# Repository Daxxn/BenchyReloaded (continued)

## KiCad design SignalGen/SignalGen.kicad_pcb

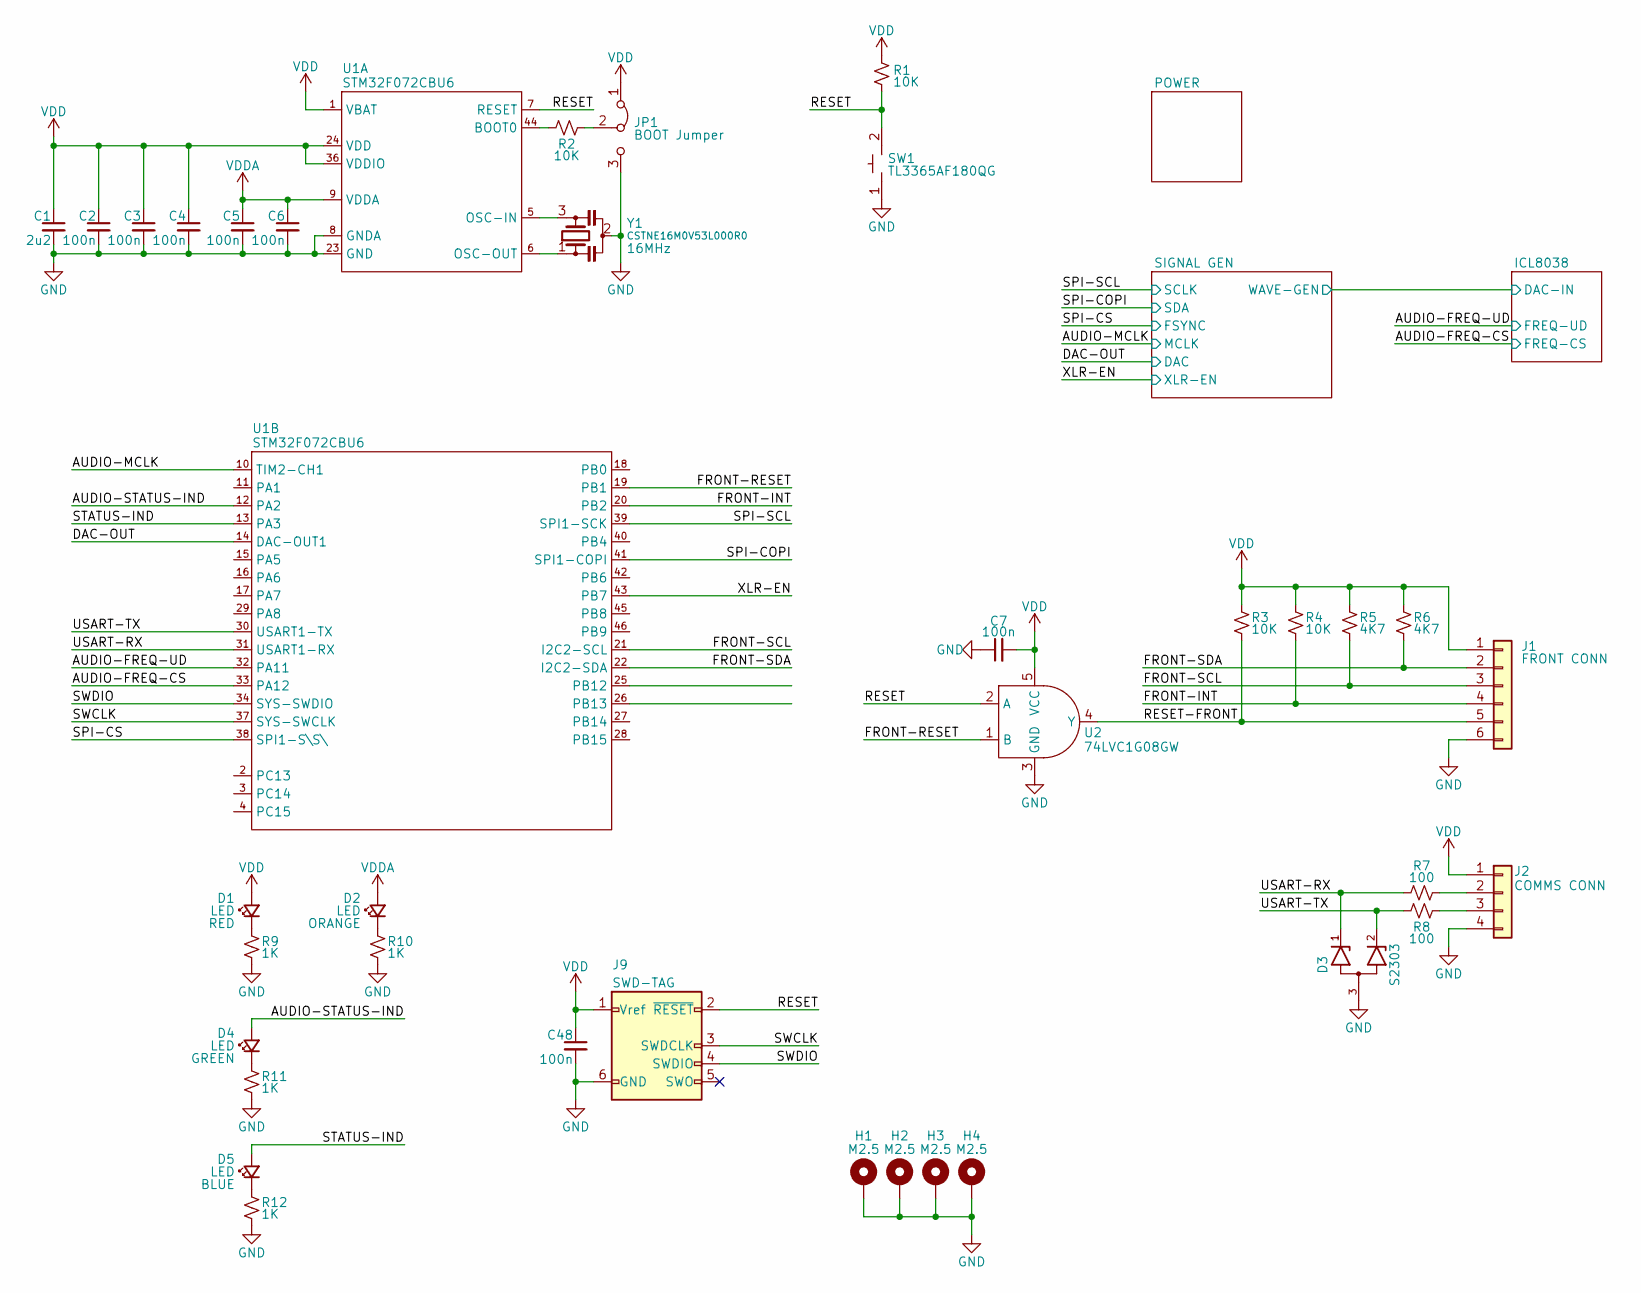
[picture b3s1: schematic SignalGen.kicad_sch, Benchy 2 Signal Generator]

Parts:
C1: 2u2; CAP_0402
C2, C3, C4, C5, C6, C7, C48: 100n; CAP_0402
D1, D2, D4, D5: LED; LED_0603_1608Metric
D3: S2303; SOT-23-3
H1, H2, H3, H4: M2.5; MountingHole_2.7mm_M2.5_DIN965_Pad
J1: FRONT CONN; JST_XH_B6B-XH-A_1x06_P2.50mm_Vertical
J2: COMMS CONN; JST_XH_B4B-XH-A_1x04_P2.50mm_Vertical
J9: SWD-TAG; Tag-Connect_TC2030-IDC-FP_2x03_P1.27mm_Vertical
JP1: BOOT Jumper; PinHeader_1x03_P2.54mm_Vertical
R1, R2, R3, R4: 10K; RES_0402
R5, R6: 4K7; RES_0402
R7, R8: 100; RES_0402
R9, R10, R11, R12: 1K; RES_0402
SW1: TL3365AF180QG
U1: STM32F072CBU6; QFN-48-1EP_7x7mm_P0.5mm_EP5.6x5.6mm
U2: 74LVC1G08GW; SOT-353_SC-70-5
Y1: CSTNE16M0V53L000R0; Resonator_SMD_3Pin_3.0x1.1mm

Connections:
/AUDIO-FREQ-CS: U1.33 (PA12); also elsewhere on the board
/AUDIO-FREQ-UD: U1.32 (PA11); also elsewhere on the board
/AUDIO-MCLK: U1.10 (TIM2-CH1); also elsewhere on the board
/AUDIO-STATUS-IND: D4.2 (A), U1.12 (PA2)
/DAC-OUT: U1.14 (DAC-OUT1); also elsewhere on the board
/FRONT-INT: J1.4, R4.2, U1.20 (PB2)
/FRONT-RESET: U1.19 (PB1), U2.1 (B)
/FRONT-SCL: J1.3, R5.2, U1.21 (I2C2-SCL)
/FRONT-SDA: J1.2, R6.2, U1.22 (I2C2-SDA)
/RESET: J9.2 (~RESET), R1.2, SW1.2, U1.7 (RESET), U2.2 (A)
/RESET-FRONT: J1.5, R3.2, U2.4 (Y)
/SPI-COPI: U1.41 (SPI1-COPI); also elsewhere on the board
/SPI-CS: U1.38 (SPI1-S\S\); also elsewhere on the board
/SPI-SCL: U1.39 (SPI1-SCK); also elsewhere on the board
/STATUS-IND: D5.2 (A), U1.13 (PA3)
/SWCLK: J9.3 (SWDCLK), U1.37 (SYS-SWCLK)
/SWDIO: J9.4 (SWDIO), U1.34 (SYS-SWDIO)
/USART-RX: D3.1 (A), R7.1, U1.31 (USART1-RX)
/USART-TX: D3.2 (B), R8.2, U1.30 (USART1-TX)
/XLR-EN: U1.43 (PB7)
GND: C1.2, C2.2, C3.2, C4.2, C5.2, C6.2, C7.1, C48.2, D3.3 (COM), H1.1, H2.1, H3.1, H4.1, J1.6, J2.4, J9.6 (GND), JP1.3 (B), R9.2, R10.2, R11.2, R12.2, SW1.1, U1.8 (GNDA), U1.23 (GND), U1.35 (GND), U1.47 (GND), U1.49 (GND), U2.3 (GND), Y1.2; also elsewhere on the board
unnamed: D1.1 (K), R9.1
unnamed: D2.1 (K), R10.1
unnamed: D4.1 (K), R11.1
unnamed: D5.1 (K), R12.1
unnamed: J2.2, R7.2
unnamed: J2.3, R8.1
unnamed: JP1.2 (C), R2.1
unnamed: R2.2, U1.44 (BOOT0)
unnamed: U1.5 (OSC-IN), Y1.3
unnamed: U1.6 (OSC-OUT), Y1.1
VDD: C1.1, C2.1, C3.1, C4.1, C7.2, C48.1, D1.2 (A), J1.1, J2.1, J9.1 (Vref), JP1.1 (A), R1.1, R3.1, R4.1, R5.1, R6.1, U1.1 (VBAT), U1.24 (VDD), U1.36 (VDDIO), U1.48 (VDD), U2.5 (VCC); also elsewhere on the board
VDDA: C5.1, C6.1, D2.2 (A), U1.9 (VDDA); also elsewhere on the board

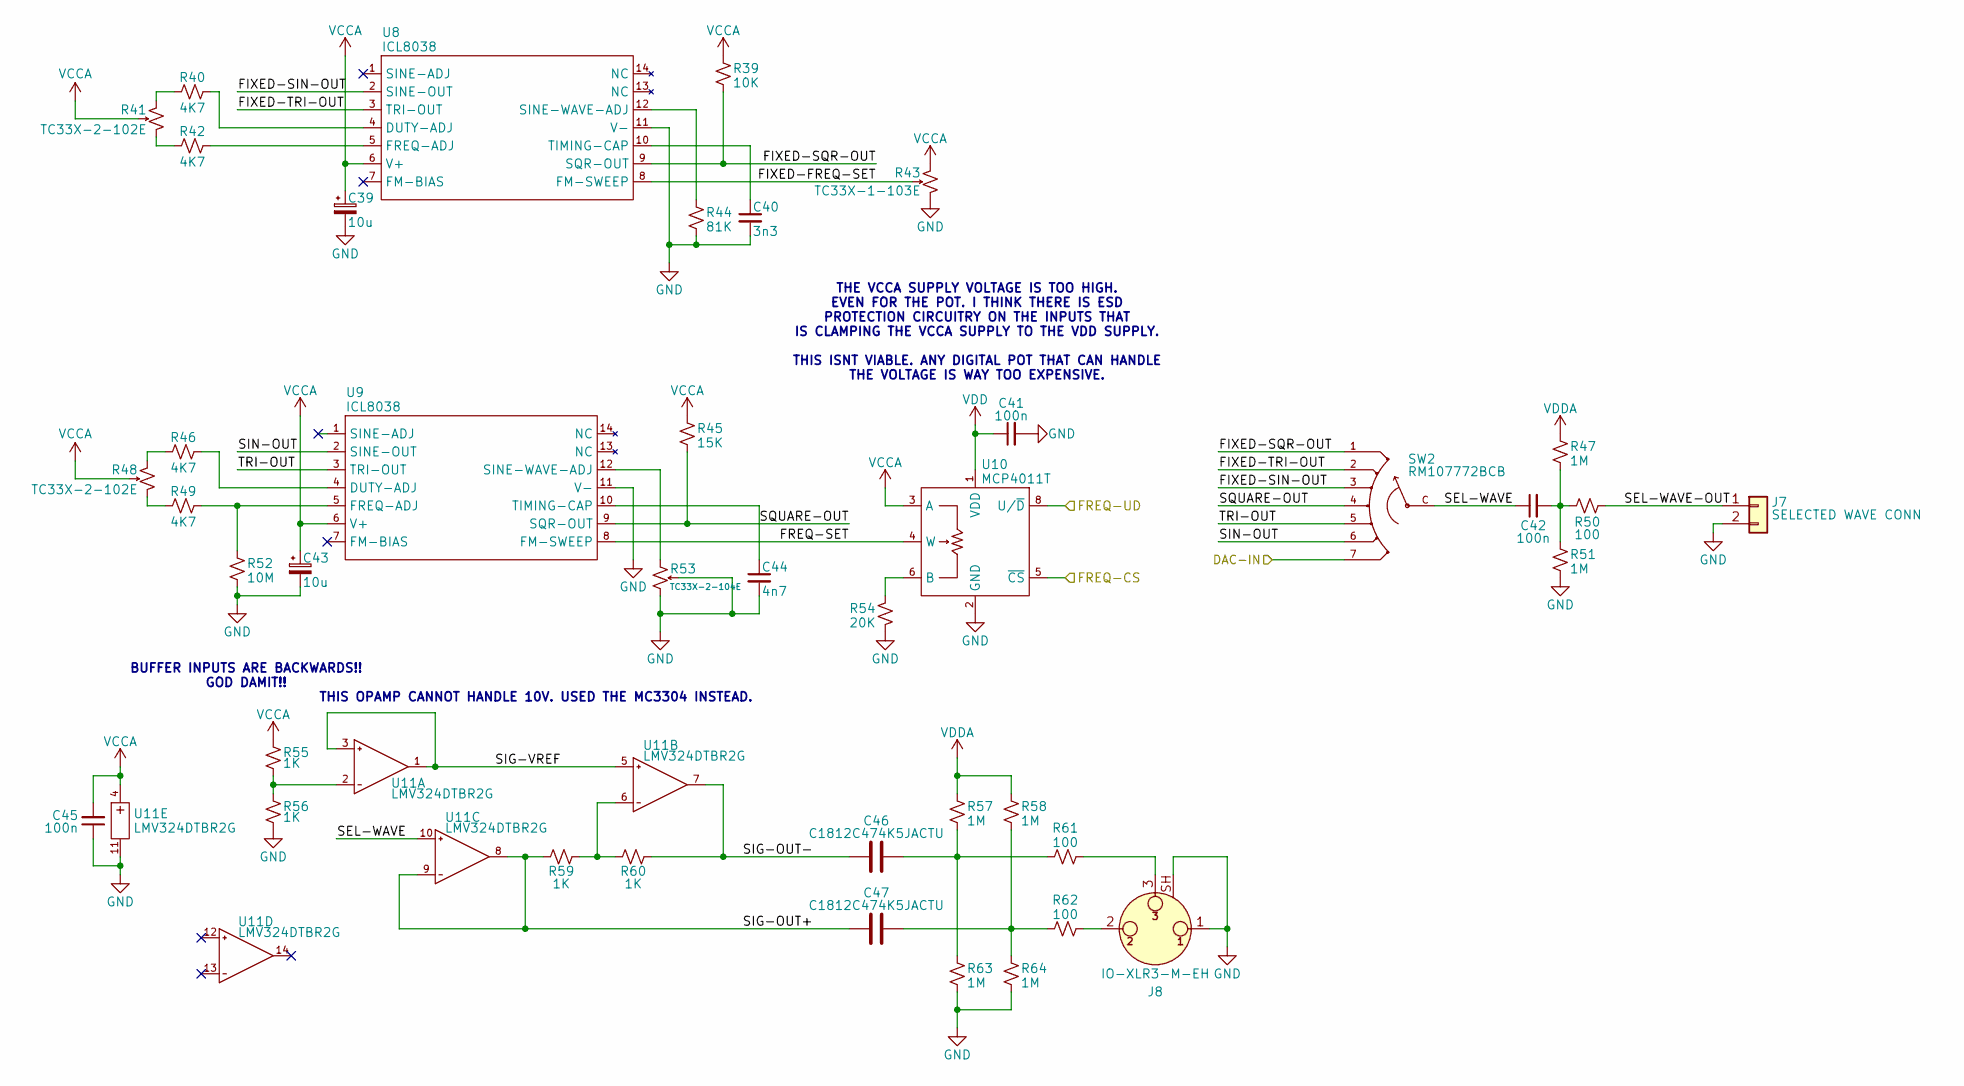
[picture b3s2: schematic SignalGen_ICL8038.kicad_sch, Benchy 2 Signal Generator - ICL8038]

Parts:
C39, C43: 10u; CAP_TAN_1206
C40: 3n3; CAP_0402
C41, C42, C45: 100n; CAP_0402
C44: 4n7; CAP_0402
C46, C47: C1812C474K5JACTU; CAP_1812
J7: SELECTED WAVE CONN; S2B-XH-A; Part Number 0311-0000-00001
J8: IO-XLR3-M-EH
R39: 10K; RES_0402
R40, R42, R46, R49: 4K7; RES_0402
R41, R48: TC33X-2-102E; Bourns_TC33X
R43: TC33X-1-103E; Bourns_TC33X
R44: 81K; RES_0402
R45: 15K; RES_0402
R47, R51, R57, R58, R63, R64: 1M; RES_0402
R50, R61, R62: 100; RES_0402
R52: 10M; RES_0402
R53: TC33X-2-104E; Bourns_TC33X
R54: 20K; RES_0402
R55, R56, R59, R60: 1K; RES_0402
SW2: RM107772BCB; RM104772BCB
U8, U9: ICL8038; DIP-14_W7.62mm
U10: MCP4011T; SOIC-8_3.9x4.9mm_P1.27mm
U11: LMV324DTBR2G; TSSOP-14_4.4x5mm_P0.65mm

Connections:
/AUDIO-FREQ-CS: U10.5 (~CS); also elsewhere on the board
/AUDIO-FREQ-UD: U10.8 (U/~D); also elsewhere on the board
/ICL8038/FIXED-FREQ-SET: R43.2, U8.8 (FM-SWEEP)
/ICL8038/FIXED-SIN-OUT: SW2.3, U8.2 (SINE-OUT)
/ICL8038/FIXED-SQR-OUT: R39.1, SW2.1, U8.9 (SQR-OUT)
/ICL8038/FIXED-TRI-OUT: SW2.2, U8.3 (TRI-OUT)
/ICL8038/FREQ-SET: U9.8 (FM-SWEEP), U10.4 (W)
/ICL8038/SEL-WAVE: C42.1, SW2.C, U11.10 (IN3+)
/ICL8038/SEL-WAVE-OUT: J7.1, R50.1
/ICL8038/SIG-OUT+: C47.1, R59.2, U11.8 (OUT3), U11.9 (IN3-)
/ICL8038/SIG-OUT-: C46.1, R60.1, U11.7 (OUT2)
/ICL8038/SIG-VREF: U11.1 (OUT1), U11.3 (IN1+), U11.5 (IN2+)
/ICL8038/SIN-OUT: SW2.6, U9.2 (SINE-OUT)
/ICL8038/SQUARE-OUT: R45.1, SW2.4, U9.9 (SQR-OUT)
/ICL8038/TRI-OUT: SW2.5, U9.3 (TRI-OUT)
/SIGNAL GEN/WAVE-GEN: SW2.7; also elsewhere on the board
GND: C39.2, C40.2, C41.2, C43.2, C44.2, C45.1, J7.2, J8.1, J8.SH, R43.3, R44.1, R51.1, R52.1, R53.2, R53.3, R54.1, R56.1, R63.1, R64.1, U8.11 (V-), U9.11 (V-), U10.2 (GND), U11.11 (V-); also elsewhere on the board
unnamed: C42.2, R47.1, R50.2, R51.2
unnamed: C46.2, R57.1, R61.1, R63.2
unnamed: C47.2, R58.1, R62.1, R64.2
unnamed: J8.2, R62.2
unnamed: J8.3, R61.2
unnamed: R40.1, R41.1
unnamed: R41.3, R42.1
unnamed: R46.1, R48.1
unnamed: R48.3, R49.1
unnamed: R40.2, U8.4 (DUTY-ADJ)
unnamed: R42.2, U8.5 (FREQ-ADJ)
unnamed: R44.2, U8.12 (SINE-WAVE-ADJ)
unnamed: C40.1, U8.10 (TIMING-CAP)
unnamed: R46.2, U9.4 (DUTY-ADJ)
unnamed: R49.2, R52.2, U9.5 (FREQ-ADJ)
unnamed: R53.1, U9.12 (SINE-WAVE-ADJ)
unnamed: C44.1, U9.10 (TIMING-CAP)
unnamed: R54.2, U10.6 (B)
unnamed: R55.1, R56.2, U11.2 (IN1-)
unnamed: R59.1, R60.2, U11.6 (IN2-)
VCCA: C39.1, C43.1, C45.2, R39.2, R41.2, R43.1, R45.2, R48.2, R55.2, U8.6 (V+), U9.6 (V+), U10.3 (A), U11.4 (V+); also elsewhere on the board
VDD: C41.1, U10.1 (VDD); also elsewhere on the board
VDDA: R47.2, R57.2, R58.2; also elsewhere on the board

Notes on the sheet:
BUFFER INPUTS ARE BACKWARDS!! GOD DAMIT!!
THIS OPAMP CANNOT HANDLE 10V. USED THE MC3304 INSTEAD.
THE VCCA SUPPLY VOLTAGE IS TOO HIGH. EVEN FOR THE POT. I THINK THERE IS ESD PROTECTION CIRCUITRY ON THE INPUTS THAT IS CLAMPING THE VCCA SUPPLY TO THE VDD SUPPLY. THIS ISNT VIABLE. ANY DIGITAL POT THAT CAN HANDLE THE VOLTAGE IS WAY TOO EXPENSIVE.

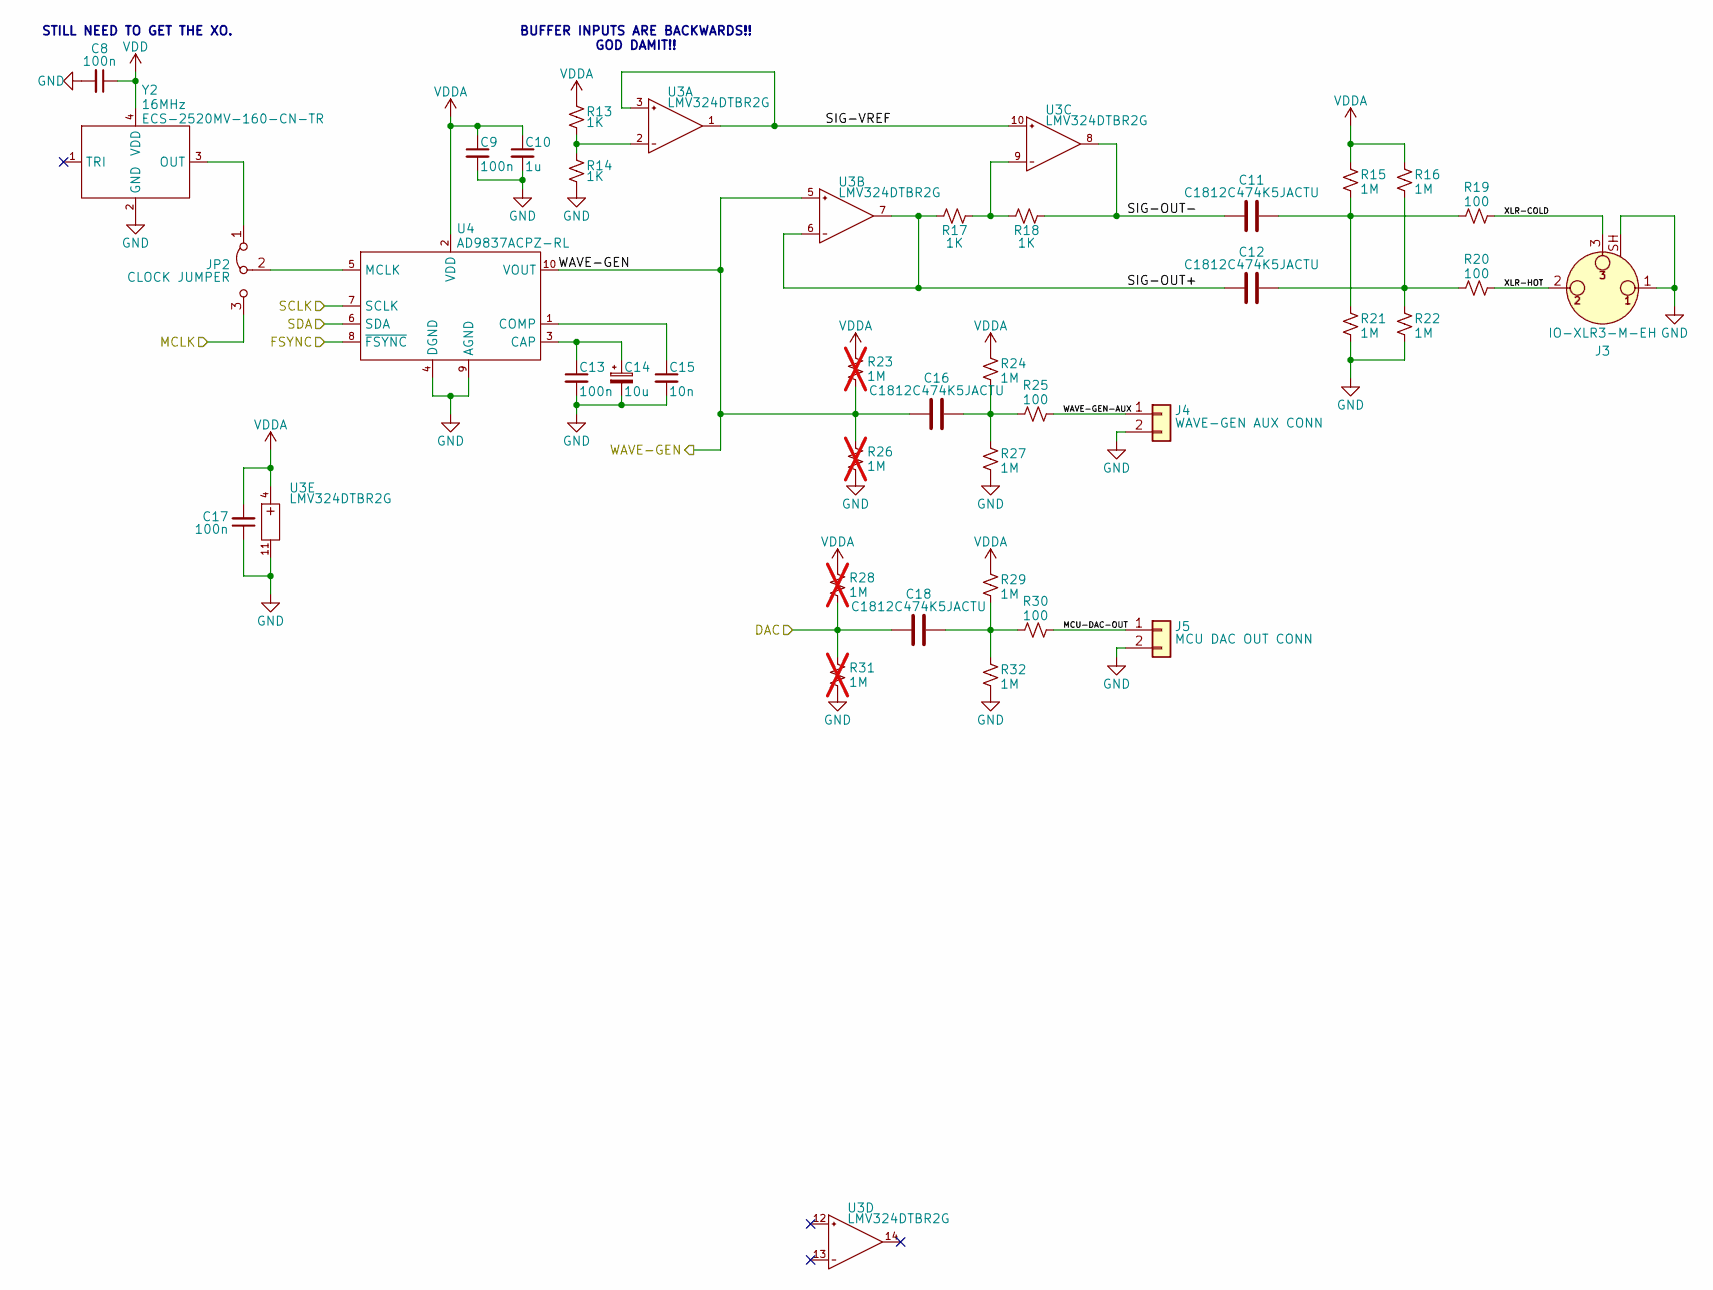
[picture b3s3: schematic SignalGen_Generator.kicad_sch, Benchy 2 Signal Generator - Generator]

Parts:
C8, C9, C13, C17: 100n; CAP_0402
C10: 1u; CAP_0402
C11, C12, C16, C18: C1812C474K5JACTU; CAP_1812
C14: 10u; CP_EIA-3216-10_Kemet-I
C15: 10n; CAP_0402
J3: IO-XLR3-M-EH
J4: WAVE-GEN AUX CONN; S2B-XH-A; Part Number 0311-0000-00001
J5: MCU DAC OUT CONN; S2B-XH-A; Part Number 0311-0000-00001
JP2: CLOCK JUMPER; SolderJumper-3_P1.3mm_Open_RoundedPad1.0x1.5mm_NumberLabels
R13, R14, R17, R18: 1K; RES_0402
R15, R16, R21, R22, R24, R27, R29, R32: 1M; RES_0402
R19, R20, R25, R30: 100; RES_0402
R23, R26, R28, R31: 1M; RES_0402; not fitted
U3: LMV324DTBR2G; TSSOP-14_4.4x5mm_P0.65mm
U4: AD9837ACPZ-RL; DFN-10-1EP_3x3mm_P0.5mm_EP1.65x2.38mm
Y2: ECS-2520MV-160-CN-TR; Crystal_SMD_4Pin_2.5x2.0mm

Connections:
/AUDIO-MCLK: JP2.3 (B); also elsewhere on the board
/DAC-OUT: C18.1, R28.1, R31.2; also elsewhere on the board
/SIGNAL GEN/MCU-DAC-OUT: J5.1, R30.2
/SIGNAL GEN/SIG-OUT+: C12.1, R17.2, U3.6 (IN2-), U3.7 (OUT2)
/SIGNAL GEN/SIG-OUT-: C11.1, R18.1, U3.8 (OUT3)
/SIGNAL GEN/SIG-VREF: U3.1 (OUT1), U3.3 (IN1+), U3.10 (IN3+)
/SIGNAL GEN/WAVE-GEN: C16.1, R23.1, R26.2, U3.5 (IN2+), U4.10 (VOUT); also elsewhere on the board
/SIGNAL GEN/WAVE-GEN-AUX: J4.1, R25.2
/SIGNAL GEN/XLR-COLD: J3.3, R19.2
/SIGNAL GEN/XLR-HOT: J3.2, R20.2
/SPI-COPI: U4.6 (SDA); also elsewhere on the board
/SPI-CS: U4.8 (~FSYNC); also elsewhere on the board
/SPI-SCL: U4.7 (SCLK); also elsewhere on the board
GND: C8.2, C9.2, C10.2, C13.2, C14.2, C15.2, C17.1, J3.1, J3.SH, J4.2, J5.2, R14.1, R21.1, R22.1, R26.1, R27.1, R31.1, R32.1, U3.11 (V-), U4.4 (DGND), U4.9 (AGND), U4.11 (DGND), Y2.2 (GND); also elsewhere on the board
unnamed: C11.2, R15.1, R19.1, R21.2
unnamed: C12.2, R16.1, R20.1, R22.2
unnamed: C16.2, R24.1, R25.1, R27.2
unnamed: C18.2, R29.1, R30.1, R32.2
unnamed: JP2.1 (A), Y2.3 (OUT)
unnamed: JP2.2 (C), U4.5 (MCLK)
unnamed: R13.1, R14.2, U3.2 (IN1-)
unnamed: R17.1, R18.2, U3.9 (IN3-)
unnamed: C13.1, C14.1, U4.3 (CAP)
unnamed: C15.1, U4.1 (COMP)
VDD: C8.1, Y2.4 (VDD); also elsewhere on the board
VDDA: C9.1, C10.1, C17.2, R13.2, R15.2, R16.2, R23.2, R24.2, R28.2, R29.2, U3.4 (V+), U4.2 (VDD); also elsewhere on the board

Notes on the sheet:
BUFFER INPUTS ARE BACKWARDS!! GOD DAMIT!!
STILL NEED TO GET THE XO.

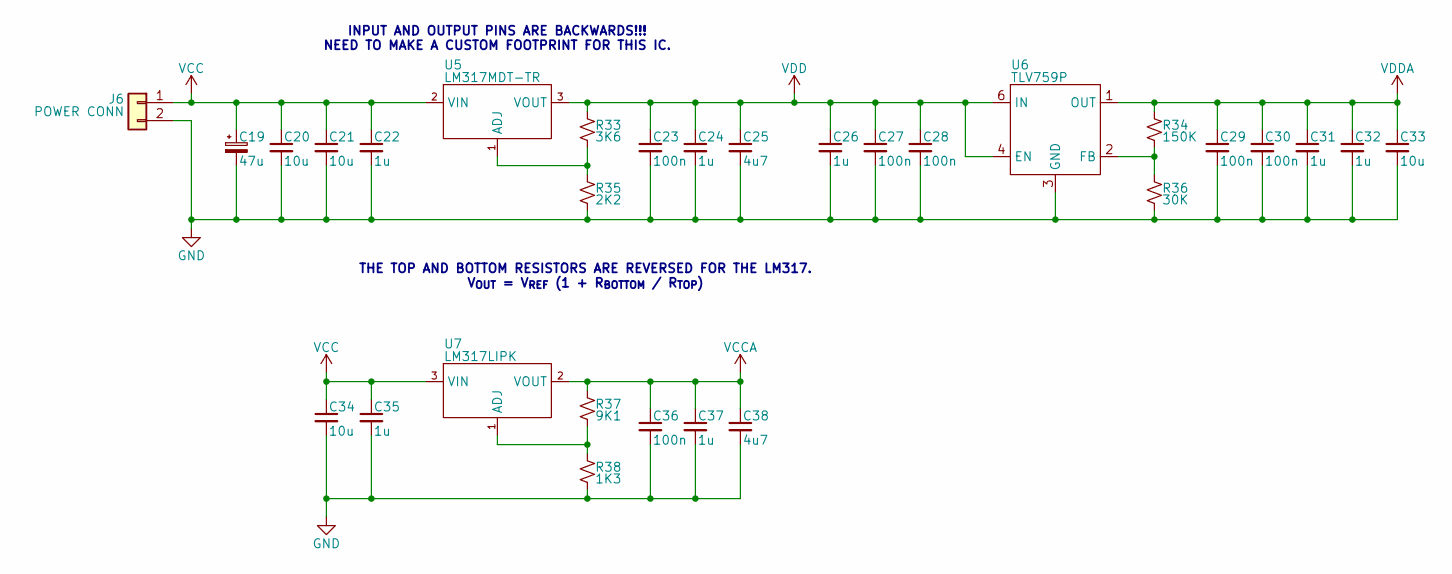
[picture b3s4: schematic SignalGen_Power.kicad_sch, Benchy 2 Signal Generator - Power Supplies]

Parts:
C19: 47u; CAP_EL_6.3x5.4
C20, C21, C34: 10u; CAP_1210
C22, C35: 1u; CAP_0805
C23, C27, C28, C29, C30, C36: 100n; CAP_0402
C24, C26, C31, C32, C37: 1u; CAP_0603
C25, C38: 4u7; CAP_0805
C33: 10u; CAP_0805
J6: POWER CONN; B2B-XH-A
R33: 3K6; RES_0402
R34: 150K; RES_0402
R35: 2K2; RES_0402
R36: 30K; RES_0402
R37: 9K1; RES_0402
R38: 1K3; RES_0402
U5: LM317MDT-TR; TO-252-2
U6: TLV759P; DFN-6-1EP_2x2mm_P0.65mm_EP1x1.6mm
U7: LM317LIPK; SOT-89-3

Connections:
GND: C19.2, C20.2, C21.2, C22.2, C23.2, C24.2, C25.2, C26.2, C27.2, C28.2, C29.2, C30.2, C31.2, C32.2, C33.2, C34.2, C35.2, C36.2, C37.2, C38.2, J6.2, R35.2, R36.2, R38.2, U6.3 (GND), U6.7 (GND); also elsewhere on the board
unnamed: R33.2, R35.1, U5.1 (ADJ)
unnamed: R34.2, R36.1, U6.2 (FB)
unnamed: R37.2, R38.1, U7.1 (ADJ)
VCC: C19.1, C20.1, C21.1, C22.1, C34.1, C35.1, J6.1, U5.2 (VIN), U7.3 (VIN)
VCCA: C36.1, C37.1, C38.1, R37.1, U7.2 (VOUT); also elsewhere on the board
VDD: C23.1, C24.1, C25.1, C26.1, C27.1, C28.1, R33.1, U5.3 (VOUT), U6.4 (EN), U6.6 (IN); also elsewhere on the board
VDDA: C29.1, C30.1, C31.1, C32.1, C33.1, R34.1, U6.1 (OUT); also elsewhere on the board

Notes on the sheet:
INPUT AND OUTPUT PINS ARE BACKWARDS!!! NEED TO MAKE A CUSTOM FOOTPRINT FOR THIS IC.
THE TOP AND BOTTOM RESISTORS ARE REVERSED FOR THE LM317. V_{OUT} = V_{REF} (1 + R_{BOTTOM} / R_{TOP})

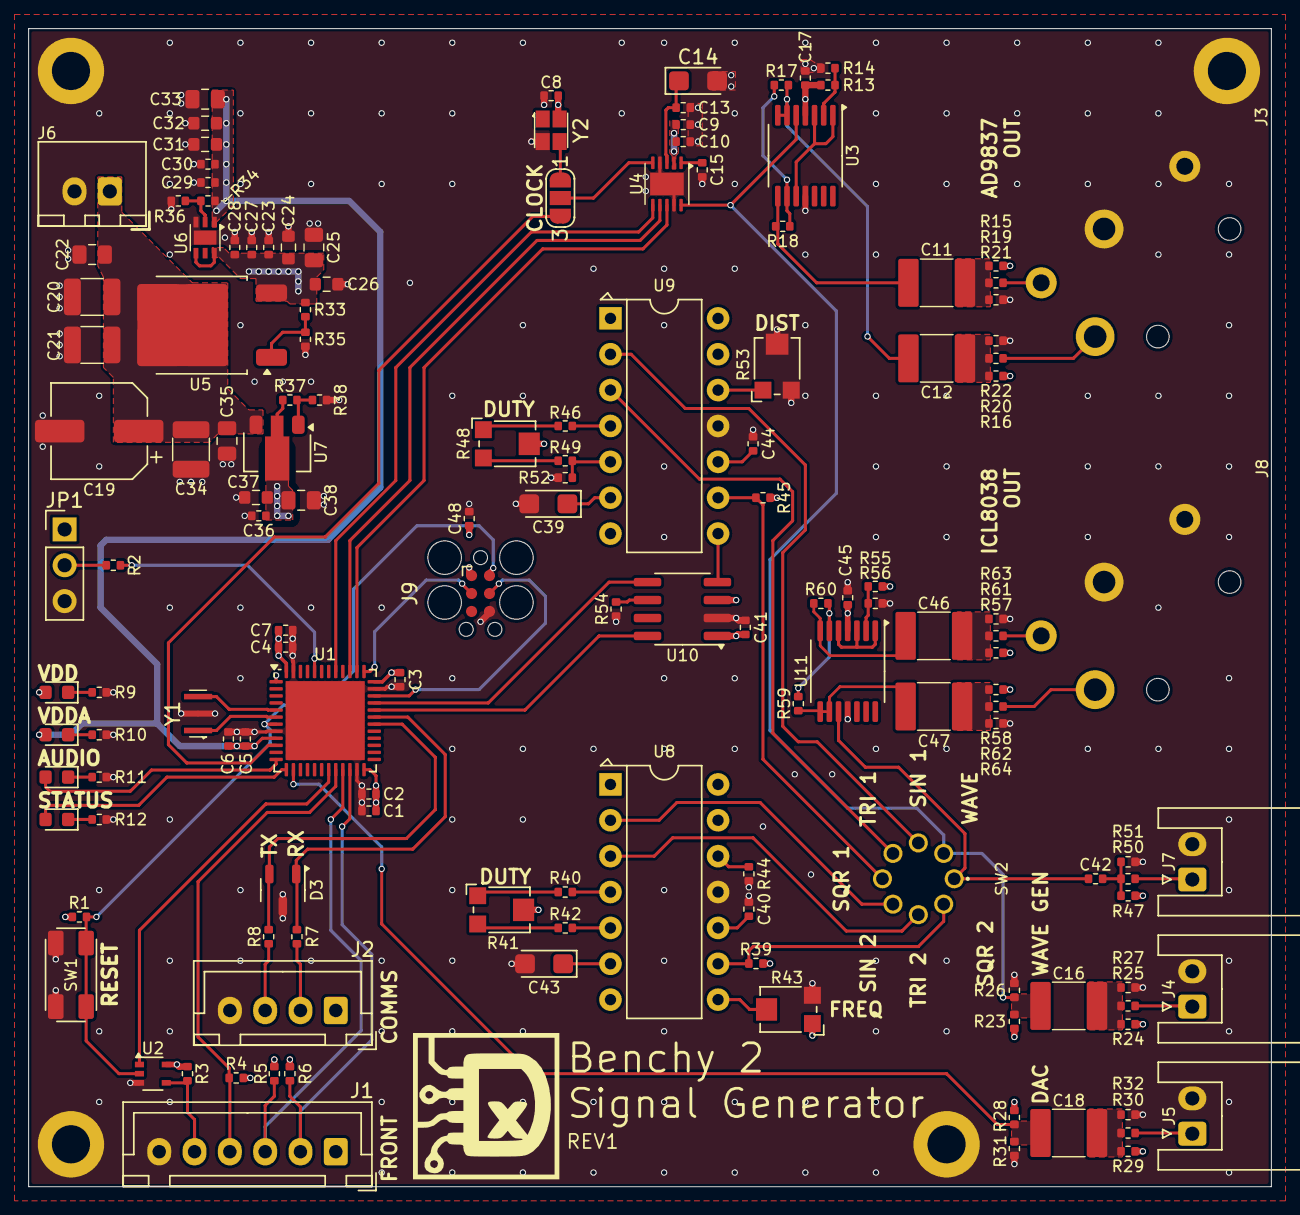
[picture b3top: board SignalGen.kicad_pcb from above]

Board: 4 copper layers, 88.0 x 82.0 mm, 147 parts (0 on the bottom side), 88 nets.

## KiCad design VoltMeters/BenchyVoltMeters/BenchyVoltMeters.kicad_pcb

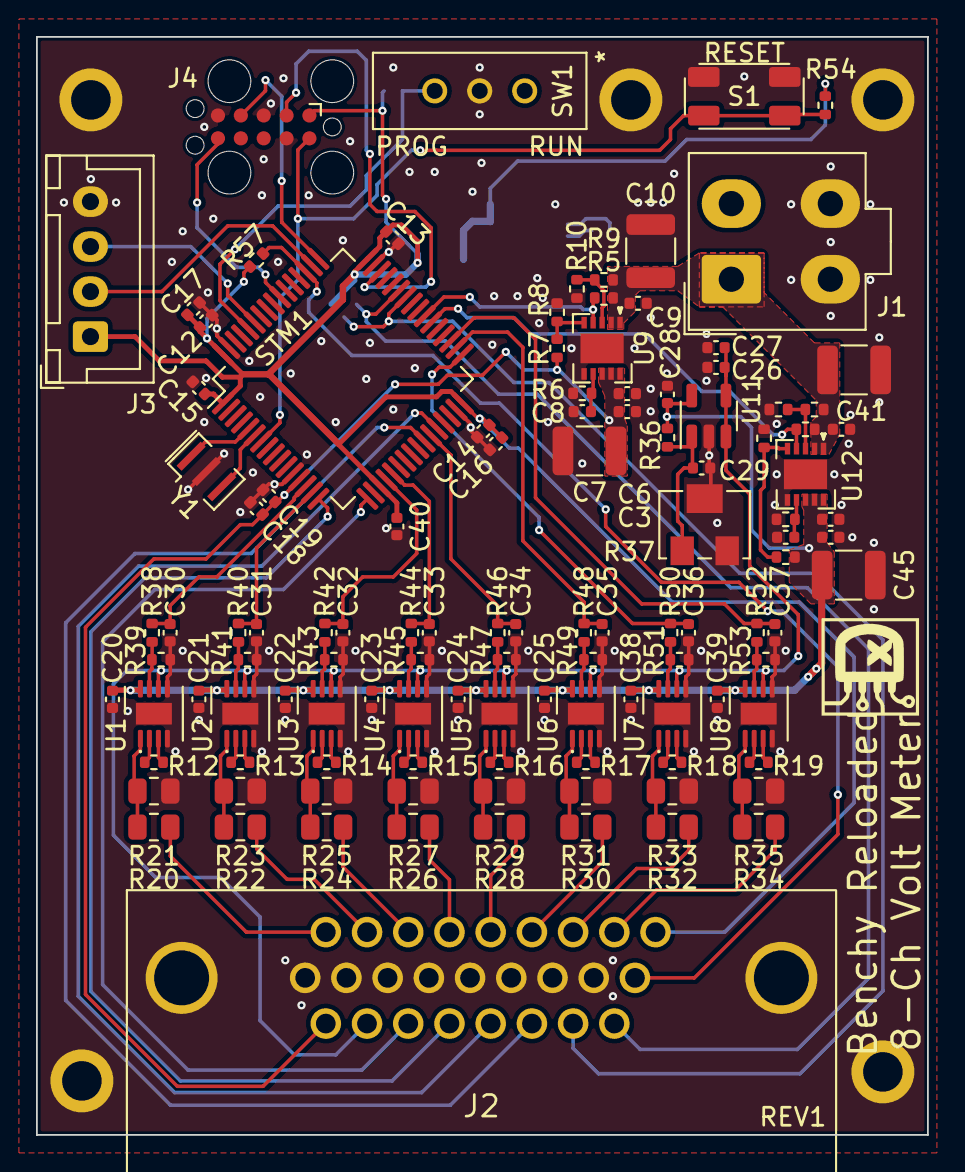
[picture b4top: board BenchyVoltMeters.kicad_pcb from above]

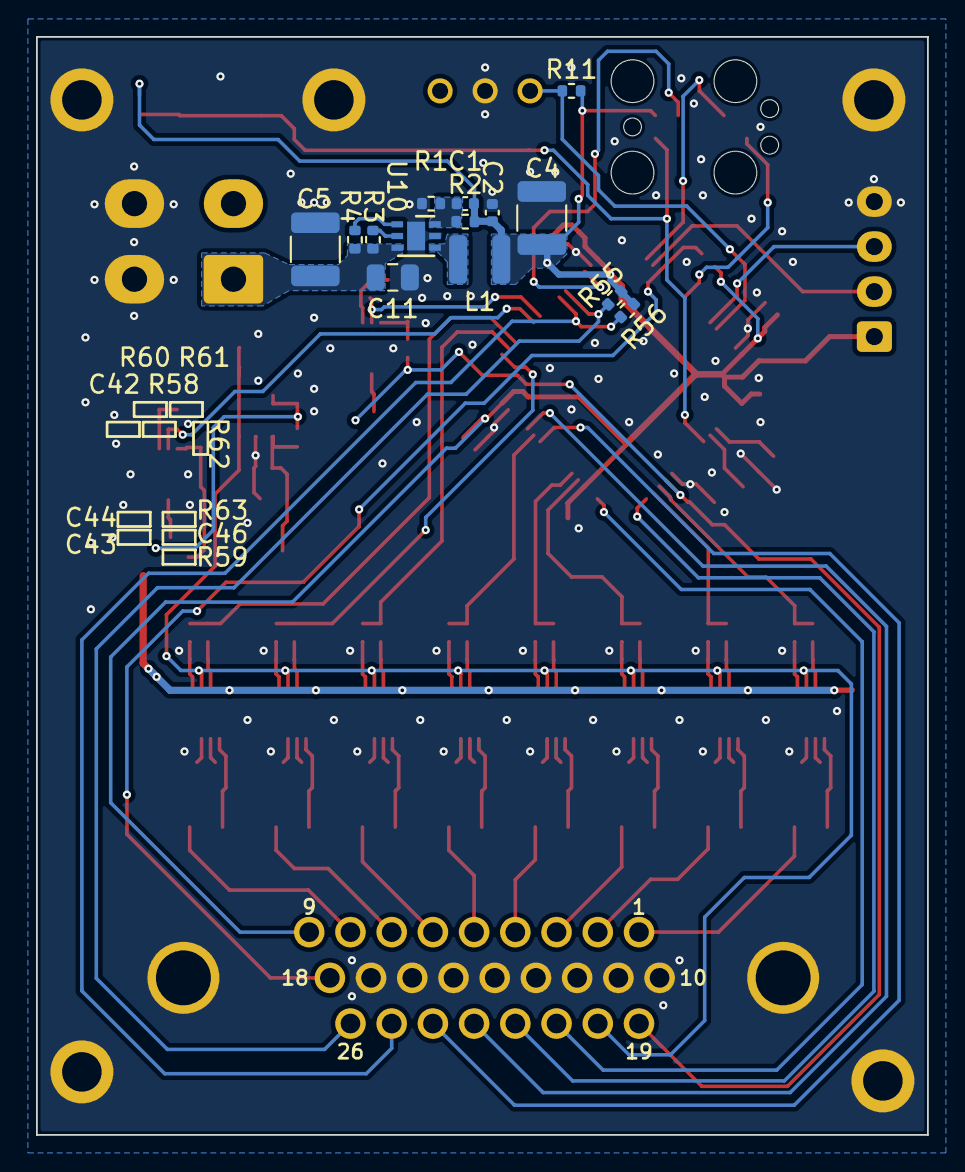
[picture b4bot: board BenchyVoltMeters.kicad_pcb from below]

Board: 2 copper layers, 49.5 x 61.0 mm, 135 parts (14 on the bottom side), 83 nets.

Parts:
C1: 22pF; C_0402_1005Metric
C2, C3, C6, C9, C20, C21, C22, C23, C24, C25, C26, C27, C28, C29, C38, C39, C42, C43, C44: 100nF; C_0402_1005Metric
C4, C5, C7, C10, C41, C45: 10uF; C_1210_3225Metric
C8, C46: 4.7uF; C_0402_1005Metric
C11: 1uF; C_0805_2012Metric
C12, C13, C14, C15, C16, C17, C18, C19, C40: 100uF; C_0402_1005Metric
C30, C31, C32, C33, C34, C35, C36, C37: 1nF; C_0402_1005Metric
H1, H2, H3, H4, H5: M2; MountingHole_2.2mm_M2_ISO7380_Pad
J1: POWER CONN; 4-Pin_Molex_Mini-Fit_Jr_Vertical
J2: DSUB-26; K66X-A26P-N
J3: MB-COMMS; JST_XH_B4B-XH-A_Vertical
J4: SWD-TAG; Tag-Connect_TC2050-IDC-FP_2x05_P1.27mm_Vertical
L1: 2.2uH; LQH3NPN
R1: 100K; R_0402_1005Metric
R2: 430K; R_0402_1005Metric
R3, R4, R5, R10, R11, R54, R57, R58, R61: 10K; R_0402_1005Metric
R6, R63: 22.1K; R_0402_1005Metric
R7, R59: 183.44K; R_0402_1005Metric
R8, R62: 12.5K; R_0402_1005Metric
R9, R60: 15K; R_0402_1005Metric
R12, R13, R14, R15, R16, R17, R18, R19: 10K 0.1%; R_0402_1005Metric
R20, R22, R24, R26, R28, R30, R32, R34: 10M 1%; R_0805_2012Metric
R21, R23, R25, R27, R29, R31, R33, R35: 256K 1%; R_0805_2012Metric
R36, R39, R41, R43, R45, R47, R49, R51, R53: 10K 1%; R_0402_1005Metric
R37: 10K; Bourns_3214W_Vertical
R38, R40, R42, R44, R46, R48, R50, R52: 100 1%; R_0402_1005Metric
R55, R56: 2.2K; R_0402_1005Metric
S1: RESET-SW; TL3365AF180QG
STM1: STM32F303RCT6TR; LQFP-64_10x10mm_P0.5mm
SW1: BOOT-SW; EG1218
U1, U2, U3, U4, U5, U6, U7, U8: INA826AIDRGR; Texas_S-PWSON-N8_EP1.2x2mm
U9, U12: TPS7A94; WSON-10-1EP_3x3mm
U10: AP3401; DFN-6-1EP_2x2mm_P0.65mm_EP1x1.6mm
U11: APX321; SOT-23-5
Y1: 8MHz; Resonator_SMD_Murata_CSTxExxV-3Pin_3.0x1.1mm

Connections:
/INT-CTRLS: J2.18, R57.2, STM1.51 (PC10)
/MC/COMP.A+: J2.21, STM1.17 (COMP2-IN+)
/MC/COMP.A-: J2.22, STM1.16 (COMP2-IN-)
/MC/COMP.B+: J2.24, STM1.26 (COMP4-IN+)
/MC/COMP.B-: J2.23, STM1.28 (COMP4-IN-)
/MC/I2C-CTRLS-SCL: J2.25, R56.1, STM1.42 (I2C2-SCL)
/MC/I2C-CTRLS-SDA: J2.26, R55.2, STM1.43 (I2C2-SDA)
/MC/I2C-MAIN-SCL: J3.2, STM1.50 (I2C1-SCL)
/MC/I2C-MAIN-SDA: J3.3, STM1.59 (I2C1-SDA)
/MC/SWCLK: J4.4 (SWDCLK), STM1.49 (SWCLK_JTCK)
/MC/SWDIO: J4.2 (SWDIO), STM1.46 (SWDIO_JTMS)
/MC/SWTRACE: J4.6 (SWO), STM1.55 (JTDO_TRACESWO)
/MC/VCCA-PG: R58.2, STM1.38 (PC7), U12.4 (PG)
/MC/VDDA-PG: R5.2, STM1.39 (PC8), U9.4 (PG)
/MC/VOLT1: C30.1, R38.2, STM1.14 (ADC1-IN1)
/MC/VOLT2: C31.1, R40.2, STM1.15 (ADC1-IN2)
/MC/VOLT3: C32.1, R42.2, STM1.20 (ADC2-IN1)
/MC/VOLT4: C33.1, R44.2, STM1.21 (ADC2-IN2)
/MC/VOLT5: C34.1, R46.2, STM1.27 (ADC3-IN1)
/MC/VOLT6: C35.1, R48.2, STM1.34 (ADC3-IN5)
/MC/VOLT7: C36.1, R50.2, STM1.33 (ADC4-IN3)
/MC/VOLT8: C37.1, R52.2, STM1.35 (ADC4-IN4)
/VOLT METERS/VOLT-IN1: J2.1, R20.2
/VOLT METERS/VOLT-IN2: J2.2, R22.2
/VOLT METERS/VOLT-IN3: J2.3, R24.2
/VOLT METERS/VOLT-IN4: J2.4, R26.2
/VOLT METERS/VOLT-IN5: J2.5, R28.2
/VOLT METERS/VOLT-IN6: J2.6, R30.2
/VOLT METERS/VOLT-IN7: J2.7, R32.2
/VOLT METERS/VOLT-IN8: J2.8, R34.2
BOOT0: R11.2, STM1.60 (BOOT0), SW1.3 (C)
GND: C2.2, C3.2, C4.2, C5.2, C6.2, C7.2, C8.1, C9.2, C10.2, C11.2, C12.2, C13.2, C14.2, C15.2, C16.2, C17.2, C18.2, C19.2, C20.2, C21.2, C22.2, C23.2, C24.2, C25.2, C26.2, C27.2, C28.2, C29.2, C30.2, C31.2, C32.2, C33.2, C34.2, C35.2, C36.2, C37.2, C38.2, C39.2, C40.2, C41.2, C42.2, C43.2, C44.2, C45.2, C46.1, H1.1, H2.1, H3.1, H4.1, H5.1, J1.3, J1.4, J2.10, J2.11, J2.12, J2.13, J2.14, J2.15, J2.16, J2.17, J2.27 (MNT), J3.4, J4.3 (GND), J4.5 (GND), J4.9 (GNDDetect), R1.2, R6.2, R8.2, R10.1, R21.1, R23.1, R25.1, R27.1, R29.1, R31.1, R33.1, R35.1, R37.2, R37.3, R39.2, R41.2, R43.2, R45.2, R47.2, R49.2, R51.2, R53.2, R61.1, R62.2, R63.2, S1.2, STM1.12 (GNDA), STM1.31 (GND), STM1.47 (GND), STM1.63 (GND), SW1.2 (B), U1.4 (+), U1.5 (V-), U1.9 (PAD), U2.4 (+), U2.5 (V-), U2.9 (PAD), U3.4 (+), U3.5 (V-), U3.9 (PAD), U4.4 (+), U4.5 (V-), U4.9 (PAD), U5.4 (+), U5.5 (V-), U5.9 (PAD), U6.4 (+), U6.5 (V-), U6.9 (PAD), U7.4 (+), U7.5 (V-), U7.9 (PAD), U8.4 (+), U8.5 (V-), U8.9 (PAD), U9.6 (GND), U9.11 (GND), U10.5 (GND), U10.7 (GND), U11.2 (V-), U12.6 (GND), U12.11 (GND), Y1.2
unnamed: R12.1, U1.3 (RG)
unnamed: R12.2, U1.2 (RG)
unnamed: R13.1, U2.3 (RG)
unnamed: R13.2, U2.2 (RG)
unnamed: R14.1, U3.3 (RG)
unnamed: R14.2, U3.2 (RG)
unnamed: R15.1, U4.3 (RG)
unnamed: R15.2, U4.2 (RG)
unnamed: R16.1, U5.3 (RG)
unnamed: R16.2, U5.2 (RG)
unnamed: R17.1, U6.3 (RG)
unnamed: R17.2, U6.2 (RG)
unnamed: R18.1, U7.3 (RG)
unnamed: R18.2, U7.2 (RG)
unnamed: R19.1, U8.3 (RG)
unnamed: R19.2, U8.2 (RG)
unnamed: R38.1, R39.1, U1.7
unnamed: R40.1, R41.1, U2.7
unnamed: R42.1, R43.1, U3.7
unnamed: R44.1, R45.1, U4.7
unnamed: R46.1, R47.1, U5.7
unnamed: R48.1, R49.1, U6.7
unnamed: R50.1, R51.1, U7.7
unnamed: R52.1, R53.1, U8.7
unnamed: STM1.5 (OSC-IN), Y1.1
unnamed: STM1.6 (OSC-OUT), Y1.3
unnamed: R20.1, R21.2, U1.1 (-)
unnamed: R22.1, R23.2, U2.1 (-)
unnamed: R24.1, R25.2, U3.1 (-)
unnamed: R26.1, R27.2, U4.1 (-)
unnamed: R28.1, R29.2, U5.1 (-)
unnamed: R30.1, R31.2, U6.1 (-)
unnamed: R32.1, R33.2, U7.1 (-)
unnamed: R34.1, R35.2, U8.1 (-)
unnamed: R9.2, R10.2, U9.3 (EN_UV)
unnamed: R7.2, R8.1, U9.5 (FB_PG)
unnamed: C8.2, R6.1, U9.7 (NR/SS)
unnamed: R4.2, U10.1 (EN)
unnamed: C1.2, R1.1, R2.2, U10.6 (FB)
unnamed: L1.1, U10.4 (LX)
unnamed: R3.2, U10.2 (PG)
unnamed: C29.1, R36.1, R37.1, U11.1 (IN+)
unnamed: R60.2, R61.2, U12.3 (EN_UV)
unnamed: R59.2, R62.1, U12.5 (FB_PG)
unnamed: C46.2, R63.1, U12.7 (NR/SS)
RESET: J4.10 (~RESET), R54.2, S1.1, STM1.7 (~RESET)
VCC: C5.1, C9.1, C10.1, C11.1, C41.1, C42.1, J1.1, R3.1, R4.1, R5.1, R9.1, R58.1, R60.1, U9.1 (IN), U9.2 (IN), U10.3 (VIN), U12.1 (IN), U12.2 (IN)
VCCA: C20.1, C21.1, C22.1, C23.1, C24.1, C25.1, C28.1, C38.1, C39.1, C43.1, C44.1, C45.1, R36.2, R59.1, U1.8 (V+), U2.8 (V+), U3.8 (V+), U4.8 (V+), U5.8 (V+), U6.8 (V+), U7.8 (V+), U8.8 (V+), U11.5 (V+), U12.8 (SNS), U12.9 (OUT), U12.10 (OUT)
VDD: C1.1, C2.1, C4.1, C12.1, C13.1, C14.1, C15.1, C16.1, C17.1, C40.1, J2.9, J3.1, J4.1 (Vref), L1.2, R2.1, R11.1, R54.1, R55.1, R56.2, R57.1, STM1.1 (VBAT), STM1.19 (VDD), STM1.32 (VDD), STM1.48 (VDD), STM1.64 (VDD)
VDDA: C3.1, C6.1, C7.1, C18.1, C19.1, J2.19, R7.1, STM1.13 (VDDA), U9.8 (SNS), U9.9 (OUT), U9.10 (OUT)
VREF: C26.1, C27.1, J2.20, U1.6 (REF), U2.6 (REF), U3.6 (REF), U4.6 (REF), U5.6 (REF), U6.6 (REF), U7.6 (REF), U8.6 (REF), U11.3 (IN-), U11.4 (OUT)
